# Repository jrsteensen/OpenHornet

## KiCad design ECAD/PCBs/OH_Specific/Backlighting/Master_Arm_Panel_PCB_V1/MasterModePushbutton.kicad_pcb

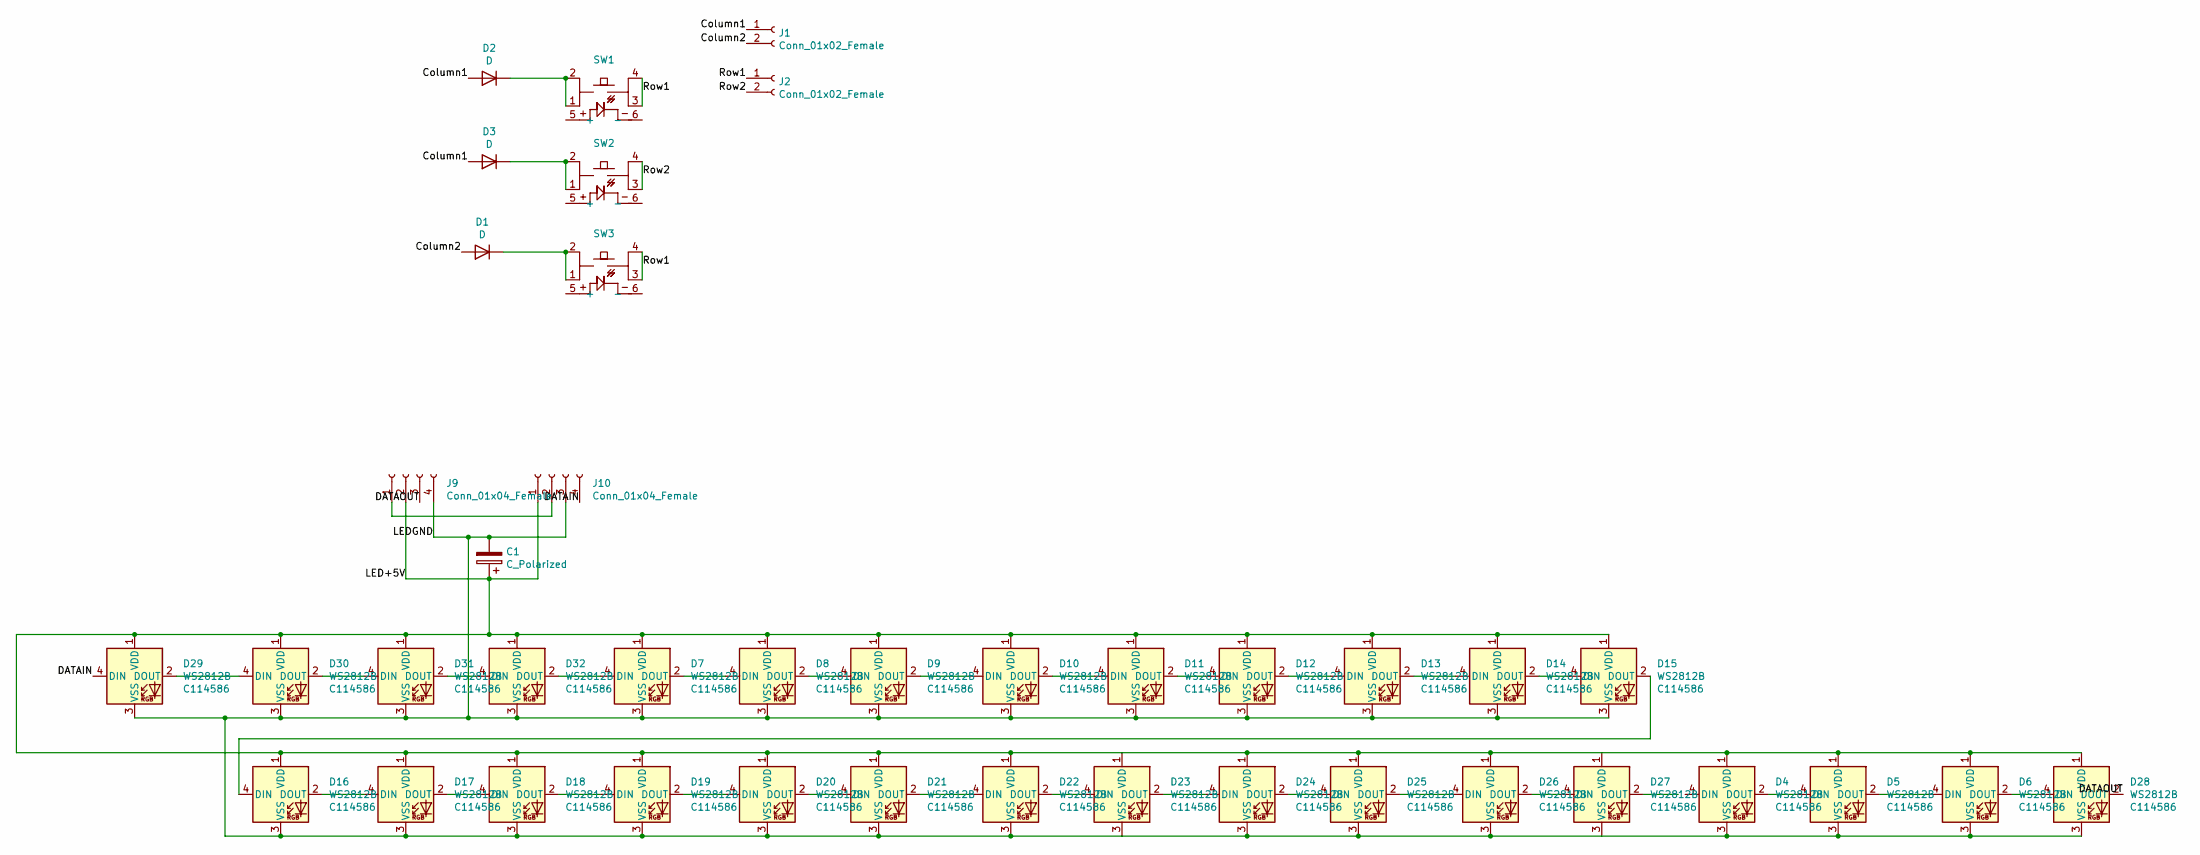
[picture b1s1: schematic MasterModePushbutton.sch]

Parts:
C1: C_Polarized; CP_Elec_8x10
D1, D2, D3: D; D_0201_0603Metric
D4, D5, D6, D28, D29, D30, D31, D32: WS2812B; LED3535; LCSC Part Number C114586
D7, D8, D9, D10, D11, D12, D13, D14, D15, D16, D17, D18, D19, D20, D21, D22, D23, D24, D25, D26, D27: WS2812B; LED_WS2812B_PLCC4_5.0x5.0mm_P3.2mm; LCSC Part Number C114586
J1, J2: Conn_01x02_Female; Molex_KK-254_AE-6410-02A_1x02_P2.54mm_Vertical
J9, J10: Conn_01x04_Female; Molex_MicroFit_2X2
SW1, SW2, SW3: PT_Tactile_Switch_Led; PT_Small_Tactile_Switch_With_LED

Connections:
/Column1: D2.2 (A), D3.2 (A), J1.1
/Column2: D1.2 (A), J1.2
/DATAIN: D29.4 (DIN), J10.4
/DATAOUT: D28.2 (DOUT), J9.3
/LED+5V: C1.1, D4.1 (VDD), D5.1 (VDD), D6.1 (VDD), D7.1 (VDD), D8.1 (VDD), D9.1 (VDD), D10.1 (VDD), D11.1 (VDD), D12.1 (VDD), D13.1 (VDD), D14.1 (VDD), D15.1 (VDD), D16.1 (VDD), D17.1 (VDD), D18.1 (VDD), D19.1 (VDD), D20.1 (VDD), D21.1 (VDD), D22.1 (VDD), D23.1 (VDD), D24.1 (VDD), D25.1 (VDD), D26.1 (VDD), D27.1 (VDD), D28.1 (VDD), D29.1 (VDD), D30.1 (VDD), D31.1 (VDD), D32.1 (VDD), J9.2, J10.1
/LEDGND: C1.2, D4.3 (VSS), D5.3 (VSS), D6.3 (VSS), D7.3 (VSS), D8.3 (VSS), D9.3 (VSS), D10.3 (VSS), D11.3 (VSS), D12.3 (VSS), D13.3 (VSS), D14.3 (VSS), D15.3 (VSS), D16.3 (VSS), D17.3 (VSS), D18.3 (VSS), D19.3 (VSS), D20.3 (VSS), D21.3 (VSS), D22.3 (VSS), D23.3 (VSS), D24.3 (VSS), D25.3 (VSS), D26.3 (VSS), D27.3 (VSS), D28.3 (VSS), D29.3 (VSS), D30.3 (VSS), D31.3 (VSS), D32.3 (VSS), J9.4, J10.3
/Row1: J2.1, SW1.3, SW1.4, SW3.3, SW3.4
/Row2: J2.2, SW2.3, SW2.4
unnamed: D1.1 (K), SW3.1, SW3.2
unnamed: D2.1 (K), SW1.1, SW1.2
unnamed: D3.1 (K), SW2.1, SW2.2
unnamed: D4.2 (DOUT), D5.4 (DIN)
unnamed: D5.2 (DOUT), D6.4 (DIN)
unnamed: D7.2 (DOUT), D8.4 (DIN)
unnamed: D8.2 (DOUT), D9.4 (DIN)
unnamed: D10.2 (DOUT), D11.4 (DIN)
unnamed: D9.2 (DOUT), D10.4 (DIN)
unnamed: D11.2 (DOUT), D12.4 (DIN)
unnamed: D12.2 (DOUT), D13.4 (DIN)
unnamed: D13.2 (DOUT), D14.4 (DIN)
unnamed: D14.2 (DOUT), D15.4 (DIN)
unnamed: D15.2 (DOUT), D16.4 (DIN)
unnamed: D16.2 (DOUT), D17.4 (DIN)
unnamed: D17.2 (DOUT), D18.4 (DIN)
unnamed: D18.2 (DOUT), D19.4 (DIN)
unnamed: D19.2 (DOUT), D20.4 (DIN)
unnamed: D20.2 (DOUT), D21.4 (DIN)
unnamed: D21.2 (DOUT), D22.4 (DIN)
unnamed: D22.2 (DOUT), D23.4 (DIN)
unnamed: D23.2 (DOUT), D24.4 (DIN)
unnamed: D24.2 (DOUT), D25.4 (DIN)
unnamed: D25.2 (DOUT), D26.4 (DIN)
unnamed: D26.2 (DOUT), D27.4 (DIN)
unnamed: D6.2 (DOUT), D28.4 (DIN)
unnamed: D29.2 (DOUT), D30.4 (DIN)
unnamed: D30.2 (DOUT), D31.4 (DIN)
unnamed: D31.2 (DOUT), D32.4 (DIN)
unnamed: D7.4 (DIN), D32.2 (DOUT)
unnamed: J9.1, J10.2

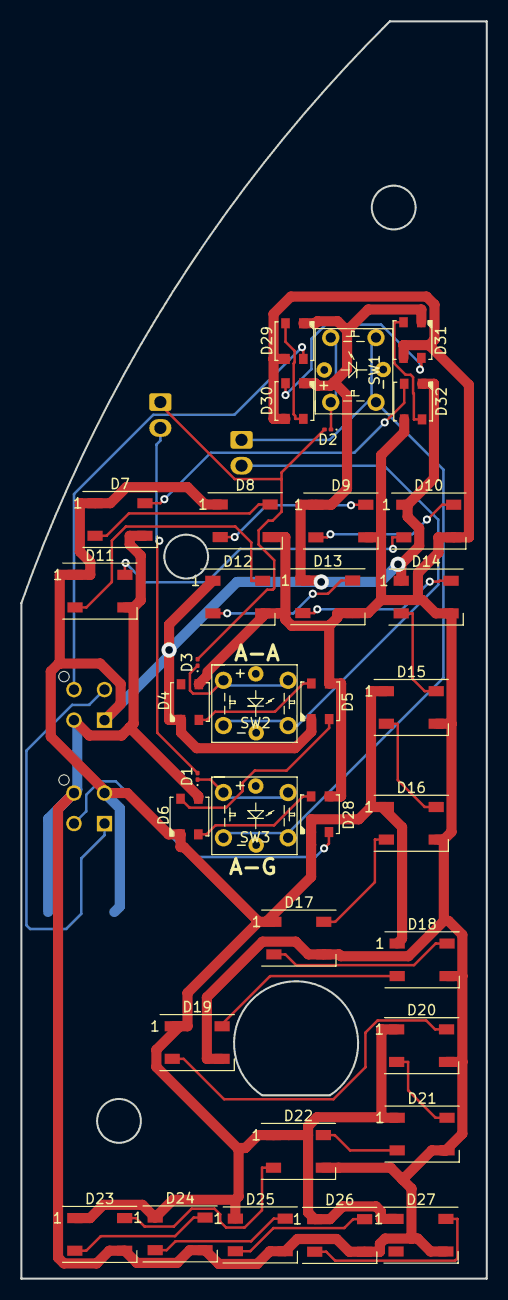
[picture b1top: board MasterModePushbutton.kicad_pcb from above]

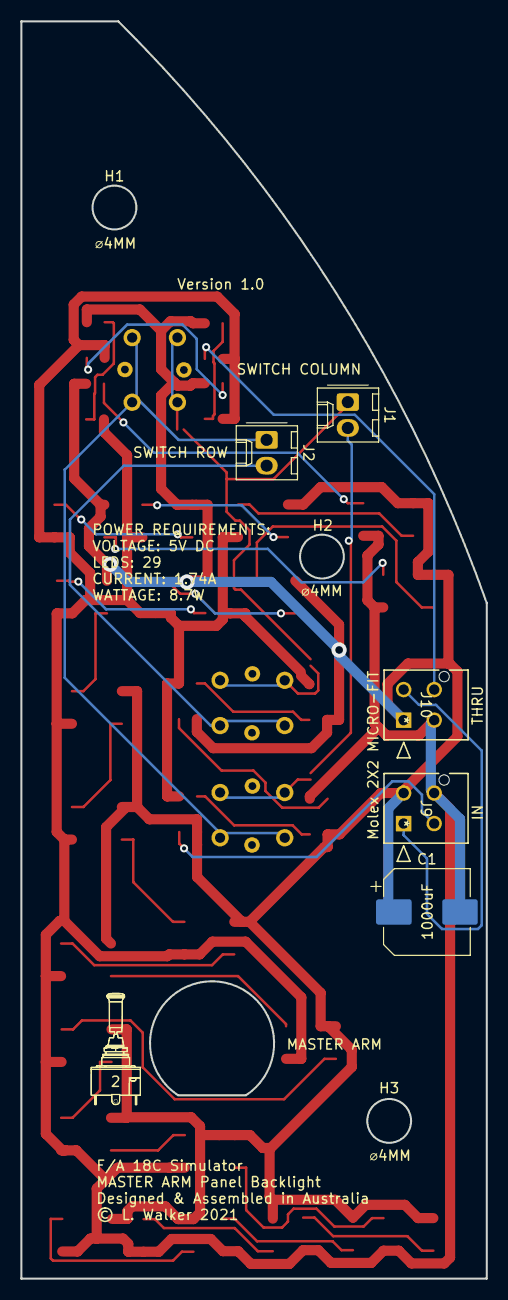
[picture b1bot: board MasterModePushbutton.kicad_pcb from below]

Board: 2 copper layers, 45.7 x 123.5 mm, 40 parts (5 on the bottom side), 39 nets.

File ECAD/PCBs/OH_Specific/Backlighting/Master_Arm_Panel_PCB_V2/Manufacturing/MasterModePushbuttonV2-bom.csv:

Comment,Designator,Footprint,LCSC
C_Polarized,C1,Capacitor_SMD:CP_Elec_8x10,
WS2812B-2020,"D4,D5,D6,D28,D29,D30,D31,D32",KiCAD Libraries:WS2812-2020,C965555
WS2812B,"D7,D8,D9,D10,D11,D12,D13,D14,D15,D16,D17,D18,D19,D20,D21,D22,D23,D24,D25,D26,D27",LED_SMD:LED_WS2812B_PLCC4_5.0x5.0mm_P3.2mm,C2761795
BL IN,J1,Connector_Molex:Molex_Mini-Fit_Jr_5566-04A_2x02_P4.20mm_Vertical,
BL OUT,J2,Connector_Molex:Molex_Mini-Fit_Jr_5566-04A_2x02_P4.20mm_Vertical,
READY,J3,Connector_Molex:Molex_KK-254_AE-6410-02A_1x02_P2.54mm_Vertical,
MASTER MODE,J4,Connector_Molex:Molex_KK-254_AE-6410-03A_1x03_P2.54mm_Vertical,
READY,SW1,Button_Switch_THT:SW_TH_Tactile_Omron_B3F-10xx,
A/A,SW2,Button_Switch_THT:SW_TH_Tactile_Omron_B3F-10xx,
A/G,SW3,Button_Switch_THT:SW_TH_Tactile_Omron_B3F-10xx,

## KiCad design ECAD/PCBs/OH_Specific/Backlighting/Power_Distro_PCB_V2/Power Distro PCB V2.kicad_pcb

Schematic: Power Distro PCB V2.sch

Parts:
D1: LED; LED_D3.0mm
J1, J2, J3, J4, J5, J6, J35: Conn_01x04_Female; Molex_Mini-Fit_Jr_5566-04A_2x02_P4.20mm_Vertical
J7: Conn_01x08_Female; PinHeader_1x08_P2.54mm_Vertical
J8, J9, J10, J11: Conn_01x04_Female; FanPinHeader_1x04_P2.54mm_Vertical
J12, J13, J14, J15, J28, J29, J30, J31, J32: Conn_01x02_Female; Molex_KK-254_AE-6410-02A_1x02_P2.54mm_Vertical
J16, J17, J18, J19, J20, J21, J22, J23, J24, J25: Conn_01x02_Female; BarrelJack_Horizontal
J26: Conn_01x08_Female; PinHeader_2x04_P2.54mm_Vertical
J27: Conn_01x24_Female; Molex_Mini-Fit_Jr_5566-24A_2x12_P4.20mm_Vertical
J33: Conn_01x03_Female; PinHeader_1x03_P2.54mm_Vertical
J34: Conn_01x02_Female; AMASS_XT60-M_1x02_P7.20mm_Vertical
R1: R; R_Axial_DIN0207_L6.3mm_D2.5mm_P7.62mm_Horizontal

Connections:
/12VSOCKETS+: J21.1, J22.1, J23.1, J24.1, J25.1, J27.10, J27.11, J28.1, J29.1, J30.1, J31.1, J33.1
/FAN1Control: J8.4, J26.2
/FAN1Tach: J8.3, J26.1
/FAN2Control: J9.4, J26.4
/FAN2Tach: J9.3, J26.3
/FAN3Control: J10.4, J26.6
/FAN3Tach: J10.3, J26.5
/FAN4Control: J11.4, J26.8
/FAN4Tach: J11.3, J26.7
/FAN+: J8.2, J9.2, J10.2, J11.2, J33.2
/LED5V1: J1.1, J1.2, J2.1, J2.2, J3.1, J3.2, J4.1, J4.2, J5.1, J5.2, J6.1, J6.2, J12.1, J13.1, J14.1, J15.1, J16.1, J17.1, J18.1, J19.1, J20.1, J27.4, J27.6, J27.21, J27.22, J27.23, J33.3, J34.2, J35.1, J35.2
/LEDDATA1: J1.4, J7.1
/LEDDATA2: J2.4, J7.2
/LEDDATA3: J3.4, J7.3
/LEDDATA4: J4.4, J7.4
/LEDDATA5: J5.4, J7.5
/LEDDATA6: J6.4, J7.6
/LEDDATA7: J7.7, J35.4
/LEDGND: J1.3, J2.3, J3.3, J4.3, J5.3, J6.3, J7.8, J8.1, J9.1, J10.1, J11.1, J12.2, J13.2, J14.2, J15.2, J16.2, J17.2, J18.2, J19.2, J20.2, J21.2, J22.2, J23.2, J24.2, J25.2, J27.3, J27.5, J27.7, J27.15, J27.17, J27.18, J27.19, J27.24, J28.2, J29.2, J30.2, J31.2, J32.1, J34.1, J35.3, R1.1
/PSUSW: J27.16, J32.2
/PWRGOOD: D1.2 (A), J27.8
unnamed: D1.1 (K), R1.2

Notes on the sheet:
12V Sockets
5V Sockets
Fan Headers
5V LCD Pin Headers
5V LED Backlight
Data In
Fan Data IO
12V Pin Headers

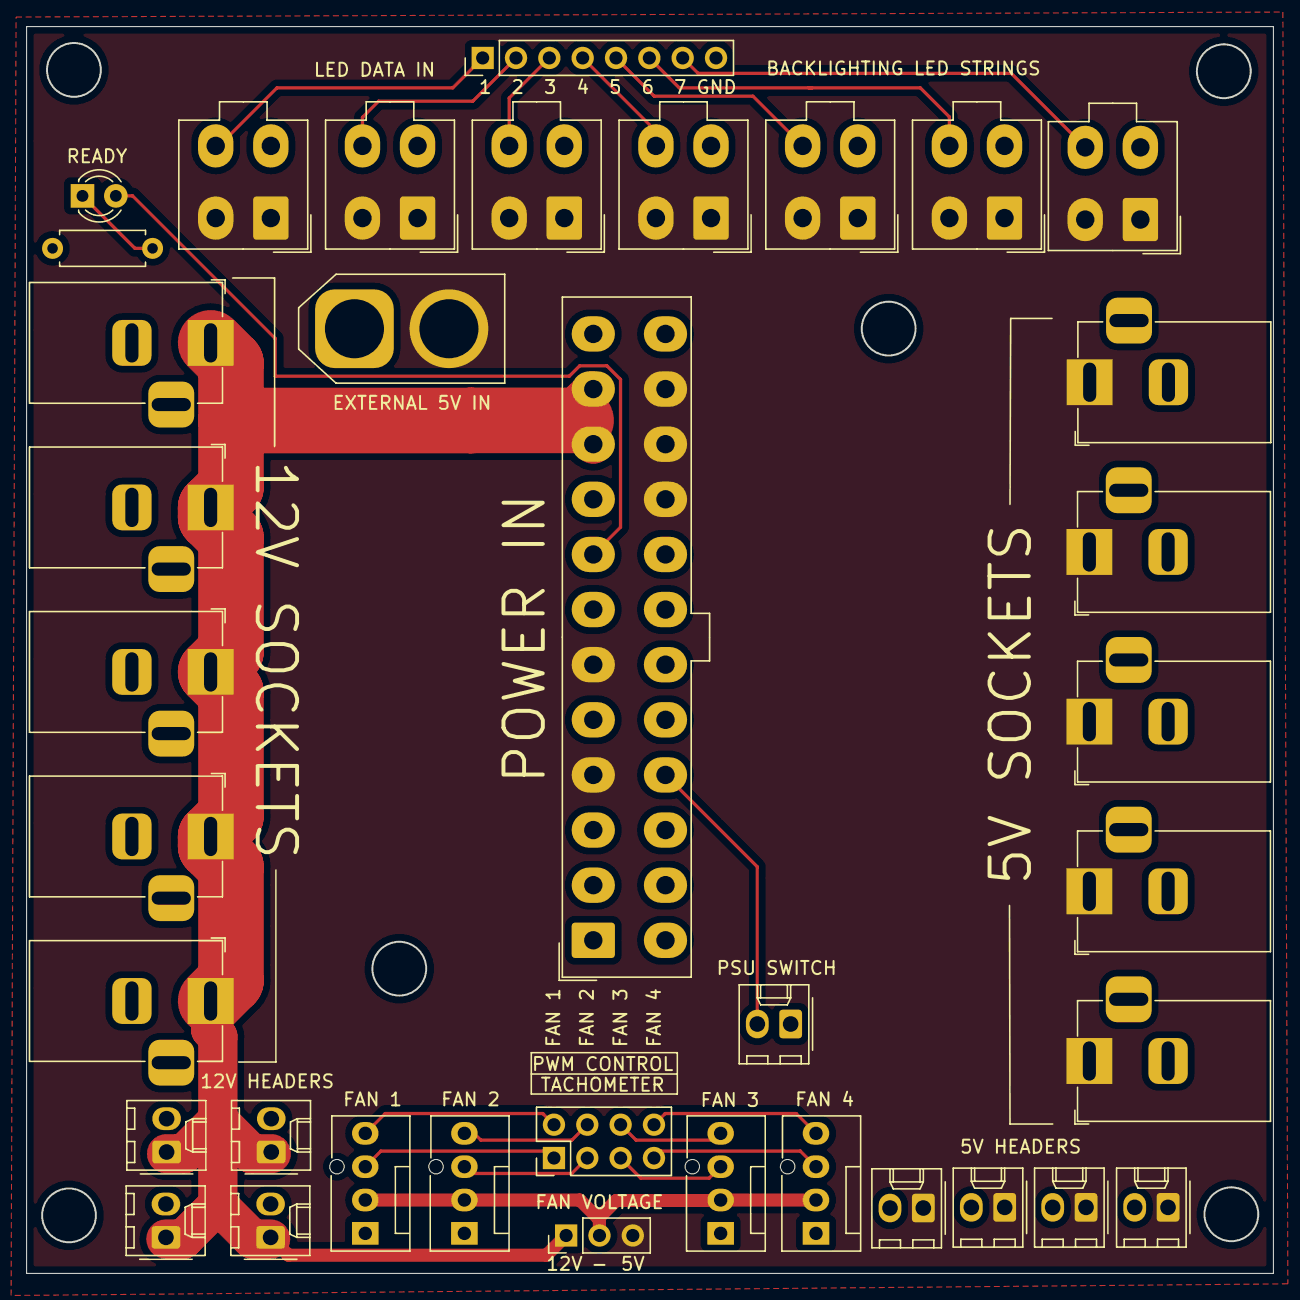
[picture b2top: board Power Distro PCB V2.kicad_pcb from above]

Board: 2 copper layers, 95.0 x 95.0 mm, 37 parts (0 on the bottom side), 22 nets.

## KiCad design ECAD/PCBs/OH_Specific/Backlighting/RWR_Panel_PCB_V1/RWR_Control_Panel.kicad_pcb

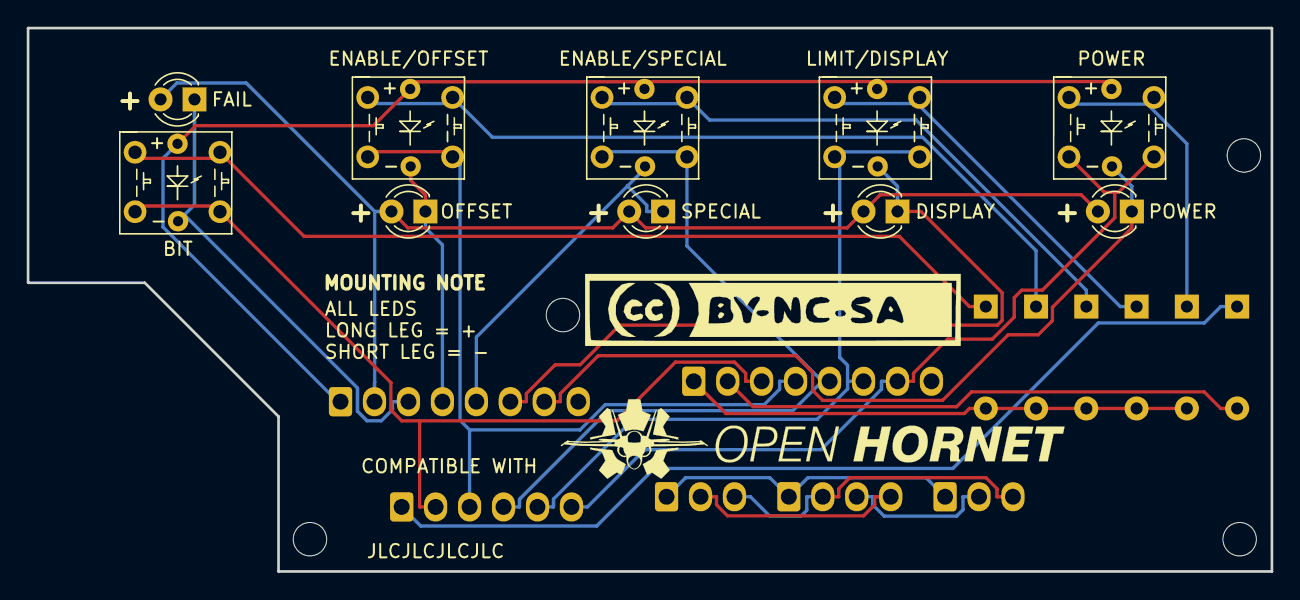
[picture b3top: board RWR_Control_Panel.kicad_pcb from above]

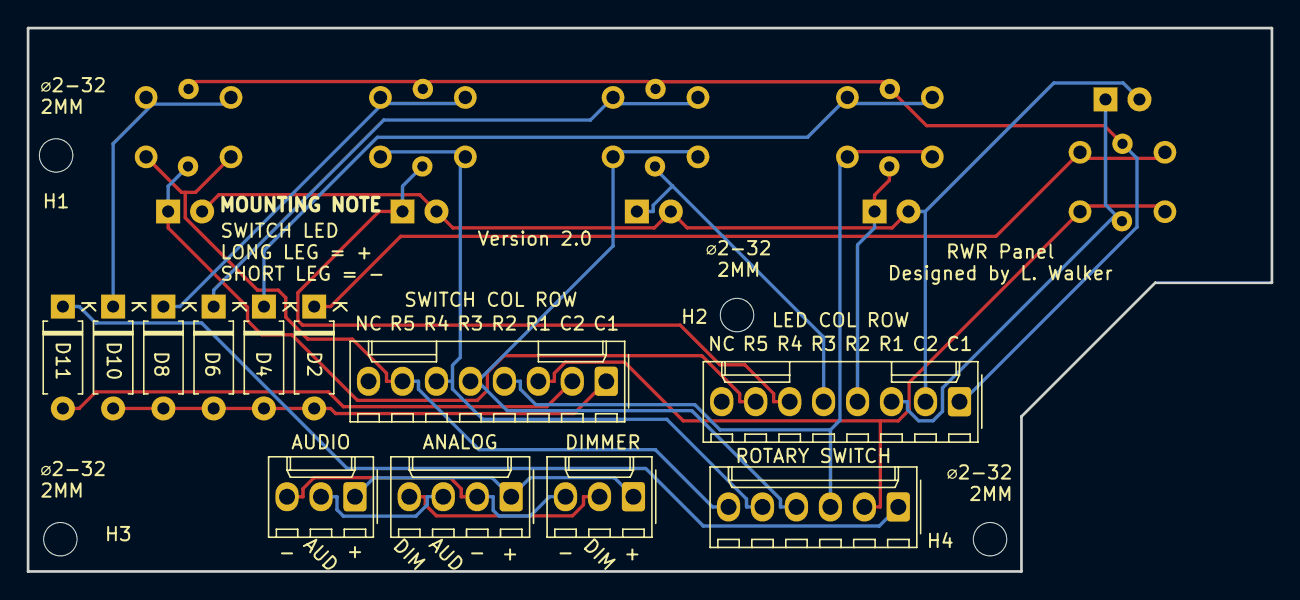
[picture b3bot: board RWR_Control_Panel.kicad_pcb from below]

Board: 2 copper layers, 93.0 x 40.6 mm, 26 parts (12 on the bottom side), 24 nets.

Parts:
BIT: PT_Tactile_Switch_Led; PT_Small_Tactile_Switch_With_LED
D1: FAIL; LED_D3.0mm
D2, D4, D6, D8, D10, D11: D; D_A-405_P7.62mm_Horizontal
D3: OFFSET; LED_D3.0mm
D5: SPECIAL; LED_D3.0mm
D7: DISPLAY; LED_D3.0mm
D9: POWER; LED_D3.0mm
ENABLE/OFFSET: PT_Tactile_Switch_Led; PT_Small_Tactile_Switch_With_LED
ENABLE/SPECIAL: PT_Tactile_Switch_Led; PT_Small_Tactile_Switch_With_LED
J1: LED COL ROW; Molex_KK-254_AE-6410-08A_1x08_P2.54mm_Vertical
J2: DIMMER; Molex_KK-254_AE-6410-03A_1x03_P2.54mm_Vertical
J3: AUDIO; Molex_KK-254_AE-6410-03A_1x03_P2.54mm_Vertical
J4: ROTARY SWITCH; Molex_KK-254_AE-6410-06A_1x06_P2.54mm_Vertical
J5: ANALOG; Molex_KK-254_AE-6410-04A_1x04_P2.54mm_Vertical
J6: SWITCH COL ROW; Molex_KK-254_AE-6410-08A_1x08_P2.54mm_Vertical
LIMIT/DISPLAY: PT_Tactile_Switch_Led; PT_Small_Tactile_Switch_With_LED
P3, P4, P5, P6: CONN_01X01; MountingHole_2.5mm
POWER: PT_Tactile_Switch_Led; PT_Small_Tactile_Switch_With_LED

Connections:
/Analog5V: J2.1, J3.1, J5.1
/AnalogAudio: J2.2, J5.3
/AnalogDimmer: J3.2, J5.4
/AnalogGND: J2.3, J3.3, J5.2
/Col1: D2.2, D4.2, D6.2, D8.2, D10.2, J6.1
/Col2: D11.2, J6.2
/Row1: BIT.3, BIT.4, J4.2, J6.3
/Row2: ENABLE/OFFSET.3, ENABLE/OFFSET.4, J4.3, J6.4
/Row3: ENABLE/SPECIAL.3, ENABLE/SPECIAL.4, J4.4, J6.5
/Row4: J4.5, J6.6, LIMIT/DISPLAY.3, LIMIT/DISPLAY.4
/Row5: J4.6, J6.7, POWER.3, POWER.4
/ledcol1: BIT.5, ENABLE/OFFSET.5, ENABLE/SPECIAL.5, J1.1, LIMIT/DISPLAY.5, POWER.5
/ledcol2: D1.2, D3.2, D5.2, D7.2, D9.2, J1.2
/ledrow1: BIT.6, D1.1, J1.3
/ledrow2: D3.1, ENABLE/OFFSET.6, J1.4
/ledrow3: D5.1, ENABLE/SPECIAL.6, J1.5
/ledrow4: D7.1, J1.6, LIMIT/DISPLAY.6
/ledrow5: D9.1, J1.7, POWER.6
unnamed: BIT.1, BIT.2, D2.1
unnamed: D4.1, ENABLE/OFFSET.1, ENABLE/OFFSET.2
unnamed: D6.1, ENABLE/SPECIAL.1, ENABLE/SPECIAL.2
unnamed: D8.1, LIMIT/DISPLAY.1, LIMIT/DISPLAY.2
unnamed: D10.1, POWER.1, POWER.2
unnamed: D11.1, J4.1

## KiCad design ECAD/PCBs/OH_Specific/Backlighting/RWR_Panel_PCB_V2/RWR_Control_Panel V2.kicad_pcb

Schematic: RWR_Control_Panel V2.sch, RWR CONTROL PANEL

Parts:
C1: 1000 nF; CP_Elec_8x10
D1: READY; LED_D3.0mm
D2, D3, D4, D5, D6, D7, D8, D9, D10, D11, D12, D13, D14, D15, D16, D17, D18, D19, D20, D21, D22, D23, D24, D25, D26, D27, D28, D29, D30, D31, D32, D33, D34: LED; WS2812-2020; LCSC C965555
H1, H2, H3, H4: MountingHole; MountingHole_2.5mm
J1: BL IN; Molex_Mini-Fit_Jr_5566-04A_2x02_P4.20mm_Vertical
J2: BL OUT; Molex_Mini-Fit_Jr_5566-04A_2x02_P4.20mm_Vertical
J3: INPUTS; PinHeader_2x05_P2.54mm_Vertical
R1: R; R_0603_1608Metric; LCSC C23138
RV1: AUDIO; Bourns_3310Y
RV2: DMR; Bourns_3310Y
SW1: BIT; SW_TH_Tactile_Omron_B3F-10xx
SW2: OFFSET; SW_TH_Tactile_Omron_B3F-10xx
SW3: SPECIAL; SW_TH_Tactile_Omron_B3F-10xx
SW4: LIMIT; SW_TH_Tactile_Omron_B3F-10xx
SW5: POWER; SW_TH_Tactile_Omron_B3F-10xx

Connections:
+5V: J3.5, RV1.1, RV2.1
/A_AUDIO: J3.1, RV1.2
/A_DMR: J3.3, RV2.2
/BIT_SW: J3.10, SW1.1, SW1.2
/BL_+5V: C1.1, D1.1 (K), D2.4 (VSS), D3.4 (VSS), D4.4 (VSS), D5.4 (VSS), D6.4 (VSS), D7.4 (VSS), D8.4 (VSS), D9.4 (VSS), D10.4 (VSS), D11.4 (VSS), D12.4 (VSS), D13.4 (VSS), D14.4 (VSS), D15.4 (VSS), D16.4 (VSS), D17.4 (VSS), D18.4 (VSS), D19.4 (VSS), D20.4 (VSS), D21.4 (VSS), D22.4 (VSS), D23.4 (VSS), D24.4 (VSS), D25.4 (VSS), D26.4 (VSS), D27.4 (VSS), D28.4 (VSS), D29.4 (VSS), D30.4 (VSS), D31.4 (VSS), D32.4 (VSS), D33.4 (VSS), D34.4 (VSS), J1.1, J1.2, J2.1, J2.2
/BL_DATA1: D9.1 (DOUT), D10.3 (DIN)
/BL_DATA2: D17.1 (DOUT), D18.3 (DIN)
/BL_DATA3: D25.1 (DOUT), D26.3 (DIN)
/BL_DATA4: D33.1 (DOUT), D34.3 (DIN)
/BL_DIN: D2.3 (DIN), J1.4
/BL_DOUT: D34.1 (DOUT), J2.4
/LIMIT_SW: J3.4, SW4.1, SW4.2
/OFFSET_SW: J3.8, SW2.1, SW2.2
/POWER_SW: J3.2, SW5.1, SW5.2
/SPECIAL_SW: J3.6, SW3.1, SW3.2
GND: C1.2, D2.2 (GND), D3.2 (GND), D4.2 (GND), D5.2 (GND), D6.2 (GND), D7.2 (GND), D8.2 (GND), D9.2 (GND), D10.2 (GND), D11.2 (GND), D12.2 (GND), D13.2 (GND), D14.2 (GND), D15.2 (GND), D16.2 (GND), D17.2 (GND), D18.2 (GND), D19.2 (GND), D20.2 (GND), D21.2 (GND), D22.2 (GND), D23.2 (GND), D24.2 (GND), D25.2 (GND), D26.2 (GND), D27.2 (GND), D28.2 (GND), D29.2 (GND), D30.2 (GND), D31.2 (GND), D32.2 (GND), D33.2 (GND), D34.2 (GND), J1.3, J2.3, J3.7, J3.9, R1.2, RV1.3, RV2.3, SW1.3, SW1.4, SW2.3, SW2.4, SW3.3, SW3.4, SW4.3, SW4.4, SW5.3, SW5.4
unnamed: D1.2 (A), R1.1
unnamed: D2.1 (DOUT), D3.3 (DIN)
unnamed: D3.1 (DOUT), D4.3 (DIN)
unnamed: D4.1 (DOUT), D5.3 (DIN)
unnamed: D5.1 (DOUT), D6.3 (DIN)
unnamed: D6.1 (DOUT), D7.3 (DIN)
unnamed: D7.1 (DOUT), D8.3 (DIN)
unnamed: D8.1 (DOUT), D9.3 (DIN)
unnamed: D10.1 (DOUT), D11.3 (DIN)
unnamed: D11.1 (DOUT), D12.3 (DIN)
unnamed: D12.1 (DOUT), D13.3 (DIN)
unnamed: D13.1 (DOUT), D14.3 (DIN)
unnamed: D14.1 (DOUT), D15.3 (DIN)
unnamed: D15.1 (DOUT), D16.3 (DIN)
unnamed: D16.1 (DOUT), D17.3 (DIN)
unnamed: D18.1 (DOUT), D19.3 (DIN)
unnamed: D19.1 (DOUT), D20.3 (DIN)
unnamed: D20.1 (DOUT), D21.3 (DIN)
unnamed: D21.1 (DOUT), D22.3 (DIN)
unnamed: D22.1 (DOUT), D23.3 (DIN)
unnamed: D23.1 (DOUT), D24.3 (DIN)
unnamed: D24.1 (DOUT), D25.3 (DIN)
unnamed: D26.1 (DOUT), D27.3 (DIN)
unnamed: D27.1 (DOUT), D28.3 (DIN)
unnamed: D28.1 (DOUT), D29.3 (DIN)
unnamed: D29.1 (DOUT), D30.3 (DIN)
unnamed: D30.1 (DOUT), D31.3 (DIN)
unnamed: D31.1 (DOUT), D32.3 (DIN)
unnamed: D32.1 (DOUT), D33.3 (DIN)

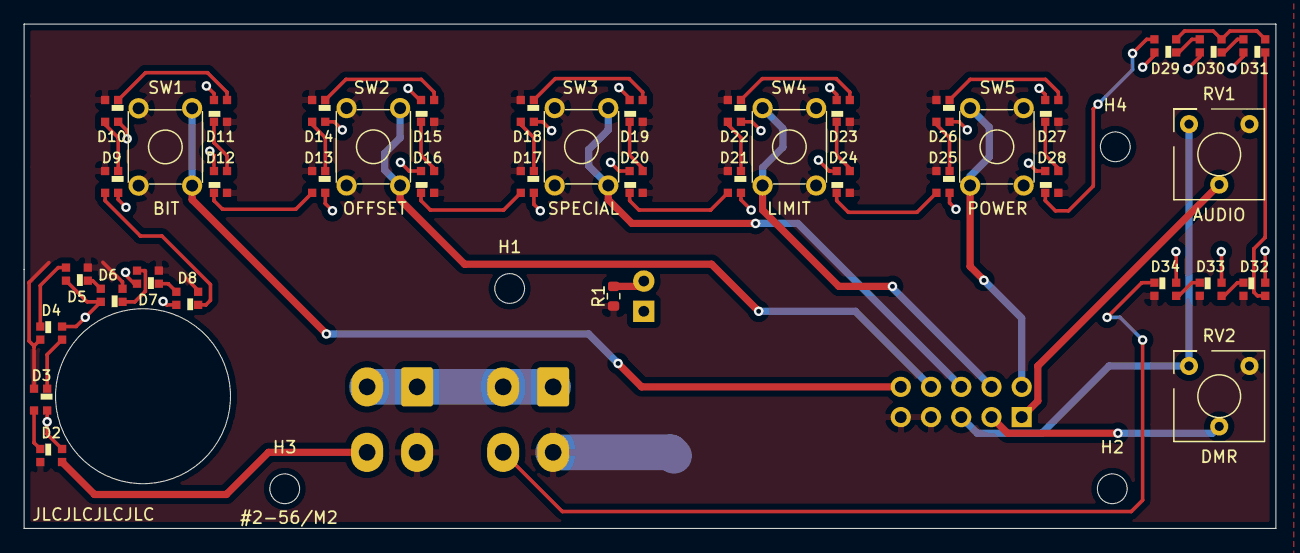
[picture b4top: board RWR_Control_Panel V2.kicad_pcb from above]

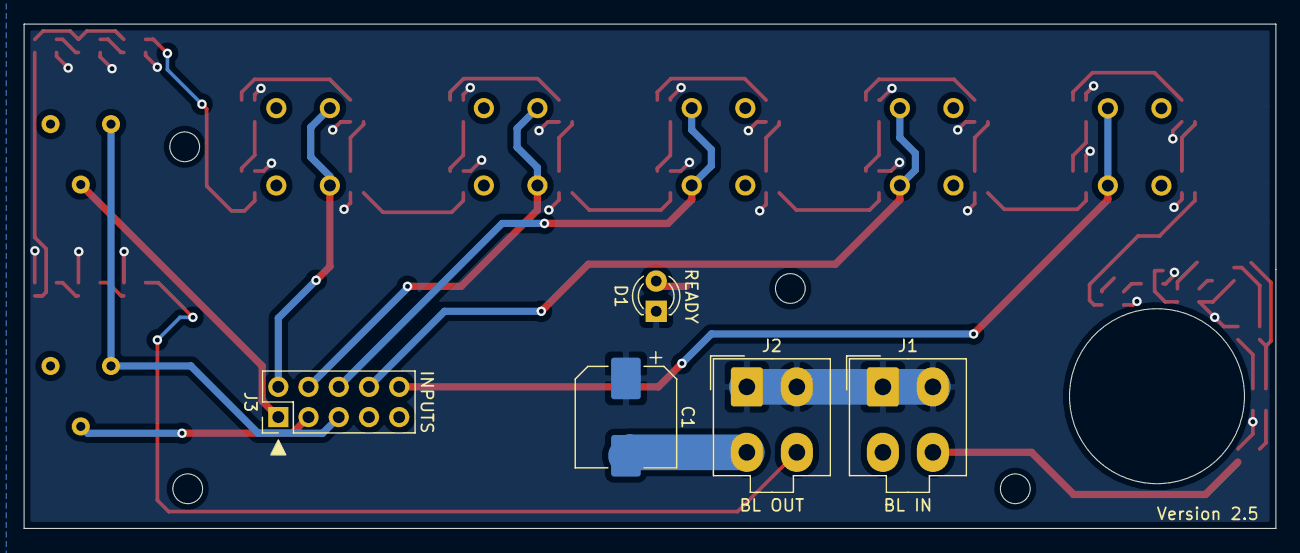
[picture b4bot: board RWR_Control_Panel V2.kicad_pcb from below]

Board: 2 copper layers, 105.2 x 42.4 mm, 50 parts (5 on the bottom side), 45 nets.

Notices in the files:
ECAD/PCBs/OH_Specific/Backlighting/Master_Arm_Panel_PCB_V1/MasterModePushbutton.kicad_pcb:
© L. Walker 2021
parts and their libraries:
Copyright 2016 Accelerated Designs. All rights reserved.
